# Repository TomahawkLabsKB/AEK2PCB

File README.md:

This is a work in progress.

This project intends to replace the orignal PCB of the Apple M3501 (Apple Extended Keyboard 2, AEK2) with a PCB powered by a Pimoroni PGA2040, which is an RP2040 breakboard board. The PGA2040 is no longer in production and not readily available for purchase.

Backstory:
I have always enjoyed the Apple M3501 and been a fan of Alps SKCM/L switches and wanted a functional way to have an AEK2 with every flavor of Alps SKCM/L I could collect. I wanted to manufacture and design as much of this project as I can. 

The main objectives of this project as as follows:

#1. Replace the original PCB with a new PCB with the following features:

  1. Native USB support
  2. Fit the M3501 case
  3. Connect to the original ADB port daughter board for USB passthrough
  4. Retain indicator LEDS and locking Capslock switch
  5. Easy access to the BOOTSEL and RESET switches for easy flashing

#2. Replace the original plate with a new aluminum plate with the following features:
  1. Fit the M3501 case using the original rubber "gaskets" on the bottom and the locking tab on top
  2. Fit original stabilizers
  3. Allow access for left and right USB breakout locations
  4. Include mounting holes on the top of the plate for future custom case mounting

Bill of Material:

| Part | Spec | Ref Numbers | Amount |
| :--- | :--- | :--- | :--- |
| Diode | 1N4148 | D1-104 | 104 |
| LED | 5mm Diffused | LED1-3 | 3 |
| LED Resistor | 1/4w 220R | R1-3 | 3 |
| USB breakout | JST XH 2.54mm 5-Pin | J1-2 | 2 |
| Polyfuse | 60R050XU | F1 | 1 |
| USB Protection | USBLC6-2SC6 | U2 | 1 |
| Reset/bootsel button | 6mm Momentary | S106-107 | 2 |
| Keyswitch | Alps SKCM\L | S1-105 | 105 |

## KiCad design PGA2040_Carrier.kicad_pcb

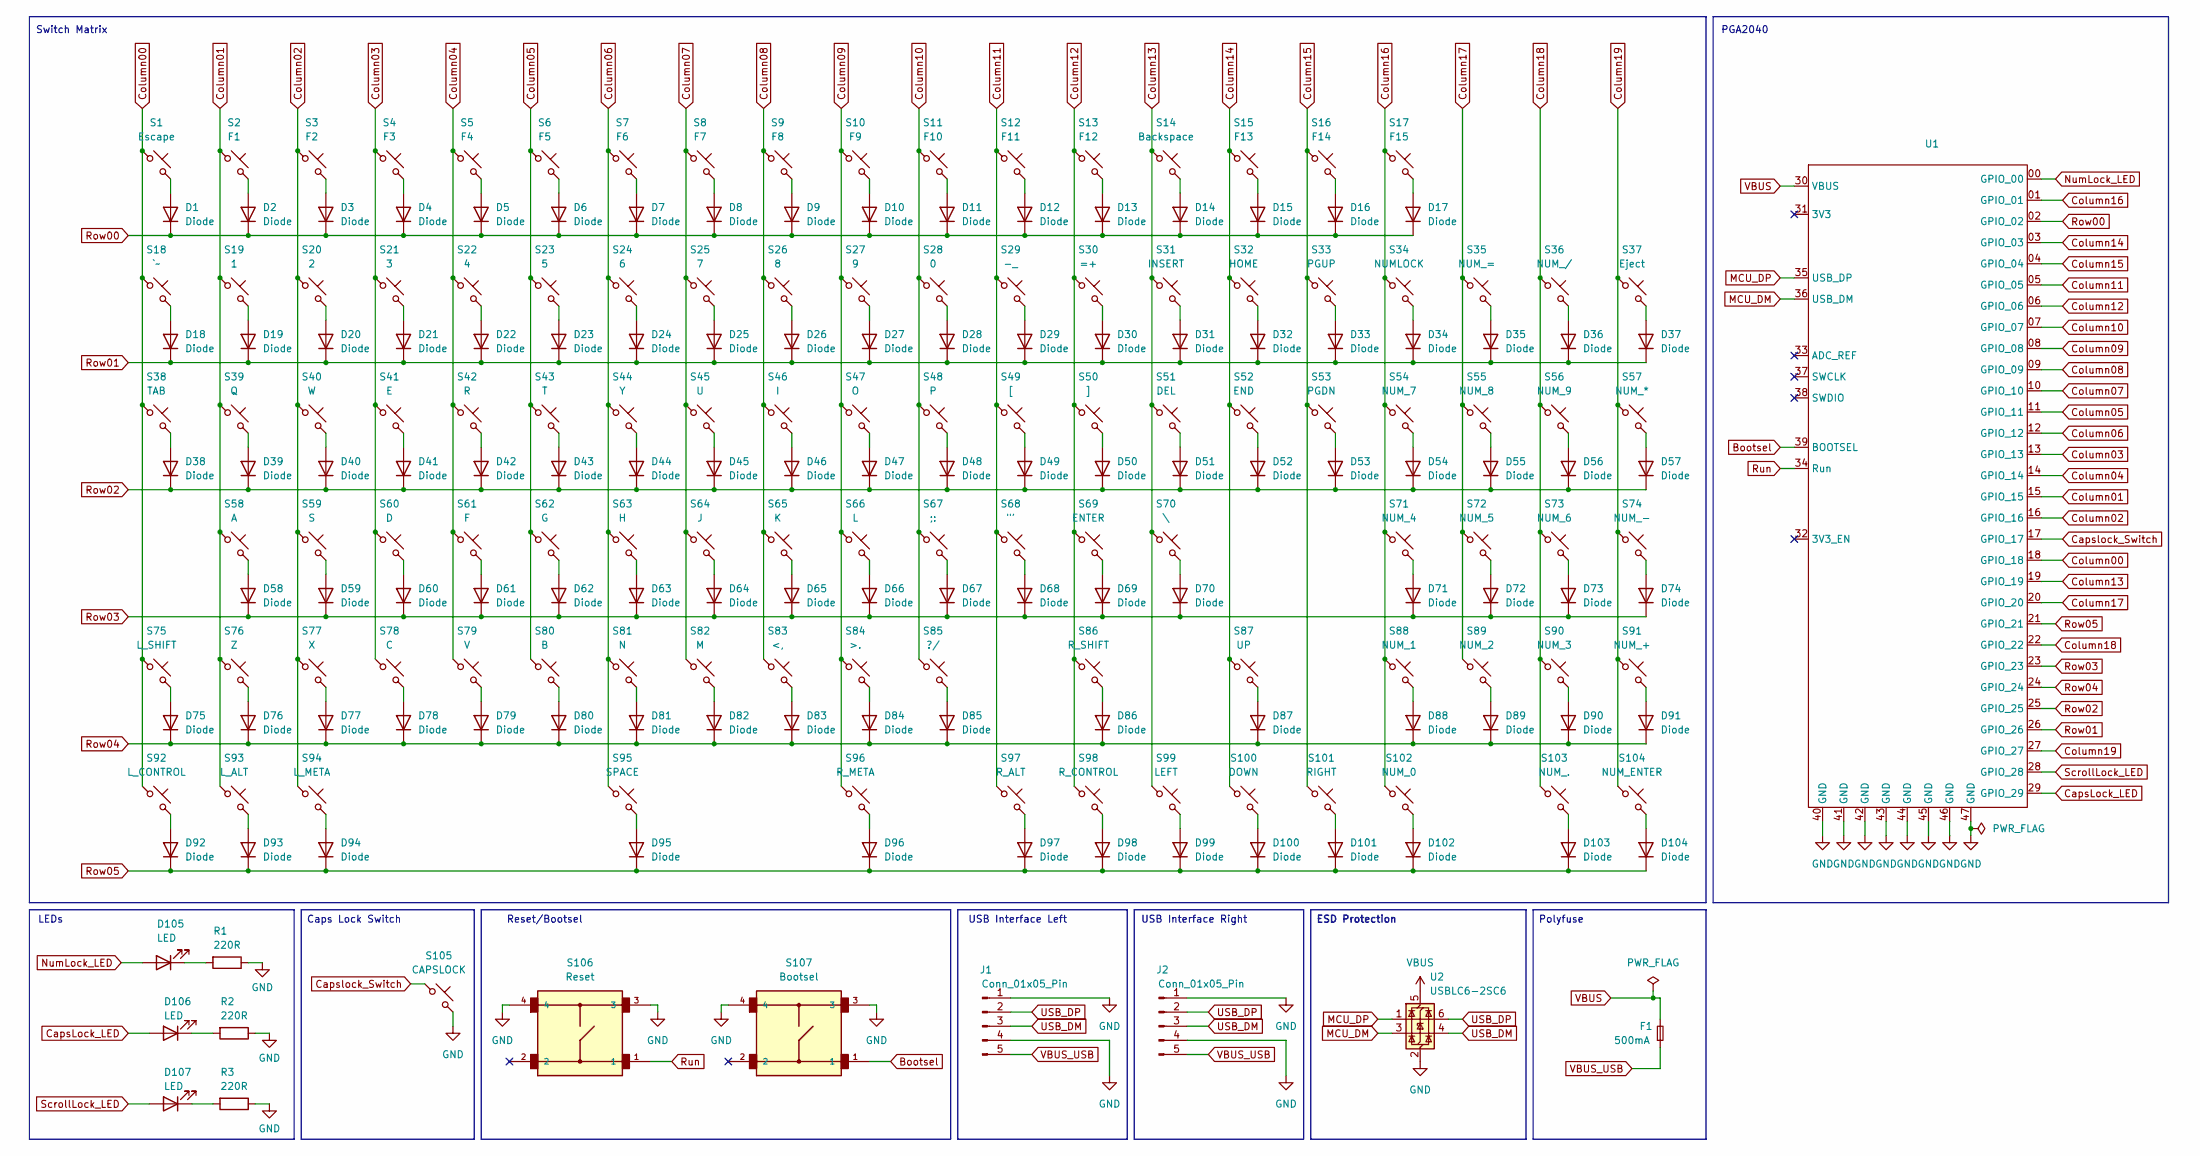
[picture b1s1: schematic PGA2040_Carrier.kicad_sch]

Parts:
D1, D2, D3, D4, D5, D6, D7, D8, D9, D10, D11, D12, D13, D14, D15, D16, D17, D18, D19, D20, D21, D22, D23, D24, D25, D26, D27, D28, D29, D30, D31, D32, D33, D34, D35, D36, D37, D38, D39, D40, D41, D42, D43, D44, D45, D46, D47, D48, D49, D50, D51, D52, D53, D54, D55, D56, D57, D58, D59, D60, D61, D62, D63, D64, D65, D66, D67, D68, D69, D70, D71, D72, D73, D74, D75, D76, D77, D78, D79, D80, D81, D82, D83, D84, D85, D86, D87, D88, D89, D90, D91, D92, D93, D94, D95, D96, D97, D98, D99, D100, D101, D102, D103, D104: Diode; THT Diode
D105, D106, D107: LED; LED_D5.0mm
F1: 500mA; Fuse_Bourns_MF-RHT050; LCSC C210357
J1, J2: Conn_01x05_Pin; PinHeader_1x05_P2.54mm_Vertical
R1, R2, R3: 220R; R_Axial_DIN0207_L6.3mm_D2.5mm_P10.16mm_Horizontal
S1: Escape; Alps_1.00u
S2: F1; Alps_1.00u
S3: F2; Alps_1.00u
S4: F3; Alps_1.00u
S5: F4; Alps_1.00u
S6: F5; Alps_1.00u
S7: F6; Alps_1.00u
S8: F7; Alps_1.00u
S9: F8; Alps_1.00u
S10: F9; Alps_1.00u
S11: F10; Alps_1.00u
S12: F11; Alps_1.00u
S13: F12; Alps_1.00u
S14: Backspace; Alps_2.00u
S15: F13; Alps_1.00u
S16: F14; Alps_1.00u
S17: F15; Alps_1.00u
S18: `~; Alps_1.00u
S19: 1; Alps_1.00u
S20: 2; Alps_1.00u
S21: 3; Alps_1.00u
S22: 4; Alps_1.00u
S23: 5; Alps_1.00u
S24: 6; Alps_1.00u
S25: 7; Alps_1.00u
S26: 8; Alps_1.00u
S27: 9; Alps_1.00u
S28: 0; Alps_1.00u
S29: -_; Alps_1.00u
S30: =+; Alps_1.00u
S31: INSERT; Alps_1.00u
S32: HOME; Alps_1.00u
S33: PGUP; Alps_1.00u
S34: NUMLOCK; Alps_1.00u
S35: NUM_=; Alps_1.00u
S36: NUM_/; Alps_1.00u
S37: Eject; Alps_1.00u
S38: TAB; Alps_1.50u
S39: Q; Alps_1.00u
S40: W; Alps_1.00u
S41: E; Alps_1.00u
S42: R; Alps_1.00u
S43: T; Alps_1.00u
S44: Y; Alps_1.00u
S45: U; Alps_1.00u
S46: I; Alps_1.00u
S47: O; Alps_1.00u
S48: P; Alps_1.00u
S49: [; Alps_1.00u
S50: ]; Alps_1.00u
S51: DEL; Alps_1.00u
S52: END; Alps_1.00u
S53: PGDN; Alps_1.00u
S54: NUM_7; Alps_1.00u
S55: NUM_8; Alps_1.00u
S56: NUM_9; Alps_1.00u
S57: NUM_*; Alps_1.00u
S58: A; Alps_1.00u
S59: S; Alps_1.00u
S60: D; Alps_1.00u
S61: F; Alps_1.00u
S62: G; Alps_1.00u
S63: H; Alps_1.00u
S64: J; Alps_1.00u
S65: K; Alps_1.00u
S66: L; Alps_1.00u
S67: ;:; Alps_1.00u
S68: "'; Alps_1.00u
S69: ENTER; Alps_2.25u
S70: \; Alps_1.50u
S71: NUM_4; Alps_1.00u
S72: NUM_5; Alps_1.00u
S73: NUM_6; Alps_1.00u
S74: NUM_-; Alps_1.00u
S75: L_SHIFT; Alps_2.25u
S76: Z; Alps_1.00u
S77: X; Alps_1.00u
S78: C; Alps_1.00u
S79: V; Alps_1.00u
S80: B; Alps_1.00u
S81: N; Alps_1.00u
S82: M; Alps_1.00u
S83: <,; Alps_1.00u
S84: >.; Alps_1.00u
S85: ?/; Alps_1.00u
S86: R_SHIFT; Alps_2.75u
S87: UP; Alps_1.00u
S88: NUM_1; Alps_1.00u
S89: NUM_2; Alps_1.00u
S90: NUM_3; Alps_1.00u
S91: NUM_+; Alps_1.00u
S92: L_CONTROL; Alps_1.50u
S93: L_ALT; Alps_1.25u
S94: L_META; Alps_1.50u
S95: SPACE; Alps_6.50u
S96: R_META; Alps_1.50u
S97: R_ALT; Alps_1.25u
S98: R_CONTROL; Alps_1.50u
S99: LEFT; Alps_1.00u
S100: DOWN; Alps_1.00u
S101: RIGHT; Alps_1.00u
S102: NUM_0; Alps_2.00u
S103: NUM_.; Alps_1.00u
S104: NUM_ENTER; Alps_2.00u
S105: CAPSLOCK; Alps_1.75u
S106: Reset; SW_B3F-1000
S107: Bootsel; SW_B3F-1000
U1: PGA2040
U2: USBLC6-2SC6; ESD_SOT-23-6; LCSC C2827654

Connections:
Bootsel: S107.1, U1.39 (BOOTSEL)
CapsLock_LED: D106.2 (A), U1.29 (GPIO_29)
Capslock_Switch: S105.1, U1.17 (GPIO_17)
Column00: S1.1, S18.1, S38.1, S75.1, S92.1, U1.18 (GPIO_18)
Column01: S2.1, S19.1, S39.1, S58.1, S76.1, S93.1, U1.15 (GPIO_15)
Column02: S3.1, S20.1, S40.1, S59.1, S77.1, S94.1, U1.16 (GPIO_16)
Column03: S4.1, S21.1, S41.1, S60.1, S78.1, U1.13 (GPIO_13)
Column04: S5.1, S22.1, S42.1, S61.1, S79.1, U1.14 (GPIO_14)
Column05: S6.1, S23.1, S43.1, S62.1, S80.1, U1.11 (GPIO_11)
Column06: S7.1, S24.1, S44.1, S63.1, S81.1, S95.1, U1.12 (GPIO_12)
Column07: S8.1, S25.1, S45.1, S64.1, S82.1, U1.10 (GPIO_10)
Column08: S9.1, S26.1, S46.1, S65.1, S83.1, U1.09 (GPIO_09)
Column09: S10.1, S27.1, S47.1, S66.1, S84.1, S96.1, U1.08 (GPIO_08)
Column10: S11.1, S28.1, S48.1, S67.1, S85.1, U1.07 (GPIO_07)
Column11: S12.1, S29.1, S49.1, S68.1, S97.1, U1.05 (GPIO_05)
Column12: S13.1, S30.1, S50.1, S69.1, S86.1, S98.1, U1.06 (GPIO_06)
Column13: S14.1, S31.1, S51.1, S70.1, S99.1, U1.19 (GPIO_19)
Column14: S15.1, S32.1, S52.1, S87.1, S100.1, U1.03 (GPIO_03)
Column15: S16.1, S33.1, S53.1, S101.1, U1.04 (GPIO_04)
Column16: S17.1, S34.1, S54.1, S71.1, S88.1, S102.1, U1.01 (GPIO_01)
Column17: S35.1, S55.1, S72.1, S89.1, U1.20 (GPIO_20)
Column18: S36.1, S56.1, S73.1, S90.1, S103.1, U1.22 (GPIO_22)
Column19: S37.1, S57.1, S74.1, S91.1, S104.1, U1.27 (GPIO_27)
GND: J1.1, J1.4, J2.1, J2.4, R1.1, R2.1, R3.1, S105.2, S106.3, S106.4, S107.3, S107.4, U1.40 (GND), U1.41 (GND), U1.42 (GND), U1.43 (GND), U1.44 (GND), U1.45 (GND), U1.46 (GND), U1.47 (GND), U2.2 (GND)
MCU_DM: U1.36 (USB_DM), U2.3 (I/O2)
MCU_DP: U1.35 (USB_DP), U2.1 (I/O1)
unnamed: D1.2 (A), S1.2
unnamed: D2.2 (A), S2.2
unnamed: D3.2 (A), S3.2
unnamed: D4.2 (A), S4.2
unnamed: D5.2 (A), S5.2
unnamed: D6.2 (A), S6.2
unnamed: D7.2 (A), S7.2
unnamed: D8.2 (A), S8.2
unnamed: D9.2 (A), S9.2
unnamed: D10.2 (A), S10.2
unnamed: D11.2 (A), S11.2
unnamed: D12.2 (A), S12.2
unnamed: D13.2 (A), S13.2
unnamed: D14.2 (A), S14.2
unnamed: D15.2 (A), S15.2
unnamed: D16.2 (A), S16.2
unnamed: D17.2 (A), S17.2
unnamed: D18.2 (A), S18.2
unnamed: D19.2 (A), S19.2
unnamed: D20.2 (A), S20.2
unnamed: D21.2 (A), S21.2
unnamed: D22.2 (A), S22.2
unnamed: D23.2 (A), S23.2
unnamed: D24.2 (A), S24.2
unnamed: D25.2 (A), S25.2
unnamed: D26.2 (A), S26.2
unnamed: D27.2 (A), S27.2
unnamed: D28.2 (A), S28.2
unnamed: D29.2 (A), S29.2
unnamed: D30.2 (A), S30.2
unnamed: D31.2 (A), S31.2
unnamed: D32.2 (A), S32.2
unnamed: D33.2 (A), S33.2
unnamed: D34.2 (A), S34.2
unnamed: D35.2 (A), S35.2
unnamed: D36.2 (A), S36.2
unnamed: D37.2 (A), S37.2
unnamed: D38.2 (A), S38.2
unnamed: D39.2 (A), S39.2
unnamed: D40.2 (A), S40.2
unnamed: D41.2 (A), S41.2
unnamed: D42.2 (A), S42.2
unnamed: D43.2 (A), S43.2
unnamed: D44.2 (A), S44.2
unnamed: D45.2 (A), S45.2
unnamed: D46.2 (A), S46.2
unnamed: D47.2 (A), S47.2
unnamed: D48.2 (A), S48.2
unnamed: D49.2 (A), S49.2
unnamed: D50.2 (A), S50.2
unnamed: D51.2 (A), S51.2
unnamed: D52.2 (A), S52.2
unnamed: D53.2 (A), S53.2
unnamed: D54.2 (A), S54.2
unnamed: D55.2 (A), S55.2
unnamed: D56.2 (A), S56.2
unnamed: D57.2 (A), S57.2
unnamed: D58.2 (A), S58.2
unnamed: D59.2 (A), S59.2
unnamed: D60.2 (A), S60.2
unnamed: D61.2 (A), S61.2
unnamed: D62.2 (A), S62.2
unnamed: D63.2 (A), S63.2
unnamed: D64.2 (A), S64.2
unnamed: D65.2 (A), S65.2
unnamed: D66.2 (A), S66.2
unnamed: D67.2 (A), S67.2
unnamed: D68.2 (A), S68.2
unnamed: D69.2 (A), S69.2
unnamed: D70.2 (A), S70.2
unnamed: D71.2 (A), S71.2
unnamed: D72.2 (A), S72.2
unnamed: D73.2 (A), S73.2
unnamed: D74.2 (A), S74.2
unnamed: D75.2 (A), S75.2
unnamed: D76.2 (A), S76.2
unnamed: D77.2 (A), S77.2
unnamed: D78.2 (A), S78.2
unnamed: D79.2 (A), S79.2
unnamed: D80.2 (A), S80.2
unnamed: D81.2 (A), S81.2
unnamed: D82.2 (A), S82.2
unnamed: D83.2 (A), S83.2
unnamed: D84.2 (A), S84.2
unnamed: D85.2 (A), S85.2
unnamed: D86.2 (A), S86.2
unnamed: D87.2 (A), S87.2
unnamed: D88.2 (A), S88.2
unnamed: D89.2 (A), S89.2
unnamed: D90.2 (A), S90.2
unnamed: D91.2 (A), S91.2
unnamed: D92.2 (A), S92.2
unnamed: D93.2 (A), S93.2
unnamed: D94.2 (A), S94.2
unnamed: D95.2 (A), S95.2
unnamed: D96.2 (A), S96.2
unnamed: D97.2 (A), S97.2
unnamed: D98.2 (A), S98.2
unnamed: D99.2 (A), S99.2
unnamed 125: D100.2 (A), S100.2; also elsewhere on the board
unnamed 126: D101.2 (A), S101.2; also elsewhere on the board
unnamed 127: D102.2 (A), S102.2; also elsewhere on the board
unnamed 128: D103.2 (A), S103.2; also elsewhere on the board
unnamed 129: D104.2 (A), S104.2; also elsewhere on the board
unnamed: D105.1 (K), R1.2
unnamed: D106.1 (K), R2.2
unnamed: D107.1 (K), R3.2
NumLock_LED: D105.2 (A), U1.00 (GPIO_00)
Row00: D1.1 (K), D2.1 (K), D3.1 (K), D4.1 (K), D5.1 (K), D6.1 (K), D7.1 (K), D8.1 (K), D9.1 (K), D10.1 (K), D11.1 (K), D12.1 (K), D13.1 (K), D14.1 (K), D15.1 (K), D16.1 (K), D17.1 (K), U1.02 (GPIO_02)
Row01: D18.1 (K), D19.1 (K), D20.1 (K), D21.1 (K), D22.1 (K), D23.1 (K), D24.1 (K), D25.1 (K), D26.1 (K), D27.1 (K), D28.1 (K), D29.1 (K), D30.1 (K), D31.1 (K), D32.1 (K), D33.1 (K), D34.1 (K), D35.1 (K), D36.1 (K), D37.1 (K), U1.26 (GPIO_26)
Row02: D38.1 (K), D39.1 (K), D40.1 (K), D41.1 (K), D42.1 (K), D43.1 (K), D44.1 (K), D45.1 (K), D46.1 (K), D47.1 (K), D48.1 (K), D49.1 (K), D50.1 (K), D51.1 (K), D52.1 (K), D53.1 (K), D54.1 (K), D55.1 (K), D56.1 (K), D57.1 (K), U1.25 (GPIO_25)
Row03: D58.1 (K), D59.1 (K), D60.1 (K), D61.1 (K), D62.1 (K), D63.1 (K), D64.1 (K), D65.1 (K), D66.1 (K), D67.1 (K), D68.1 (K), D69.1 (K), D70.1 (K), D71.1 (K), D72.1 (K), D73.1 (K), D74.1 (K), U1.23 (GPIO_23)
Row04: D75.1 (K), D76.1 (K), D77.1 (K), D78.1 (K), D79.1 (K), D80.1 (K), D81.1 (K), D82.1 (K), D83.1 (K), D84.1 (K), D85.1 (K), D86.1 (K), D87.1 (K), D88.1 (K), D89.1 (K), D90.1 (K), D91.1 (K), U1.24 (GPIO_24)
Row05: D92.1 (K), D93.1 (K), D94.1 (K), D95.1 (K), D96.1 (K), D97.1 (K), D98.1 (K), D99.1 (K), D100.1 (K), D101.1 (K), D102.1 (K), D103.1 (K), D104.1 (K), U1.21 (GPIO_21); also elsewhere on the board
Run: S106.1, U1.34 (Run)
ScrollLock_LED: D107.2 (A), U1.28 (GPIO_28)
USB_DM: J1.3, J2.3, U2.4 (I/O2)
USB_DP: J1.2, J2.2, U2.6 (I/O1)
VBUS: F1.2, U1.30 (VBUS), U2.5 (VBUS)
VBUS_USB: F1.1, J1.5, J2.5

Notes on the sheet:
USB Interface Left
Caps Lock Switch
USB Interface Right
Switch Matrix
Polyfuse
LEDs
PGA2040
ESD Protection
Reset/Bootsel

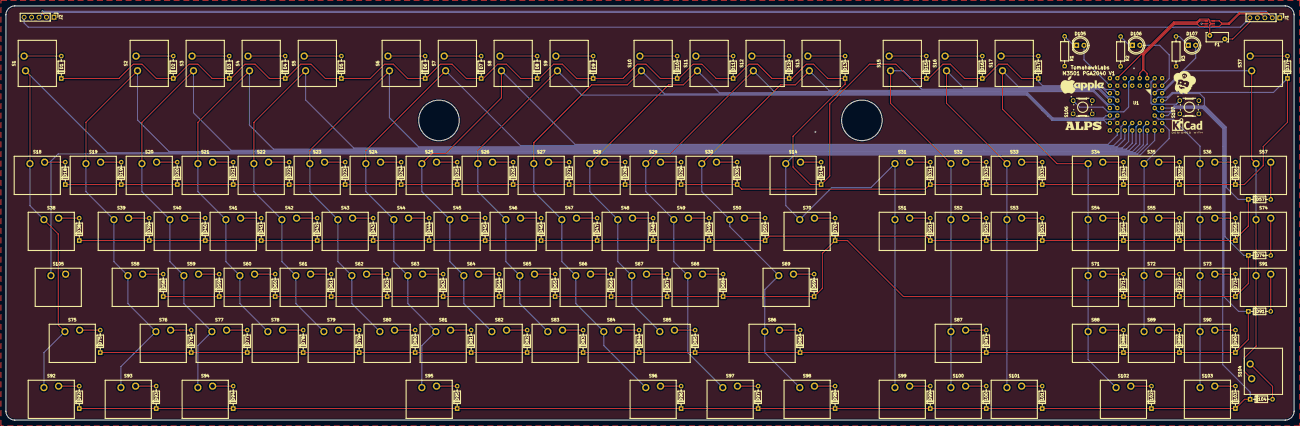
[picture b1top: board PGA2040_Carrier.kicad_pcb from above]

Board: 2 copper layers, 438.3 x 140.9 mm, 222 parts (0 on the bottom side), 146 nets.

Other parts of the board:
100, 101, 102, 103, 104: Diode; THT Diode

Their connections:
unnamed 125: 100.2 (A); also elsewhere on the board
unnamed 126: 101.2 (A); also elsewhere on the board
unnamed 127: 102.2 (A); also elsewhere on the board
unnamed 128: 103.2 (A); also elsewhere on the board
unnamed 129: 104.2 (A); also elsewhere on the board
Row05: 100.1 (K), 101.1 (K), 102.1 (K), 103.1 (K), 104.1 (K); also elsewhere on the board
